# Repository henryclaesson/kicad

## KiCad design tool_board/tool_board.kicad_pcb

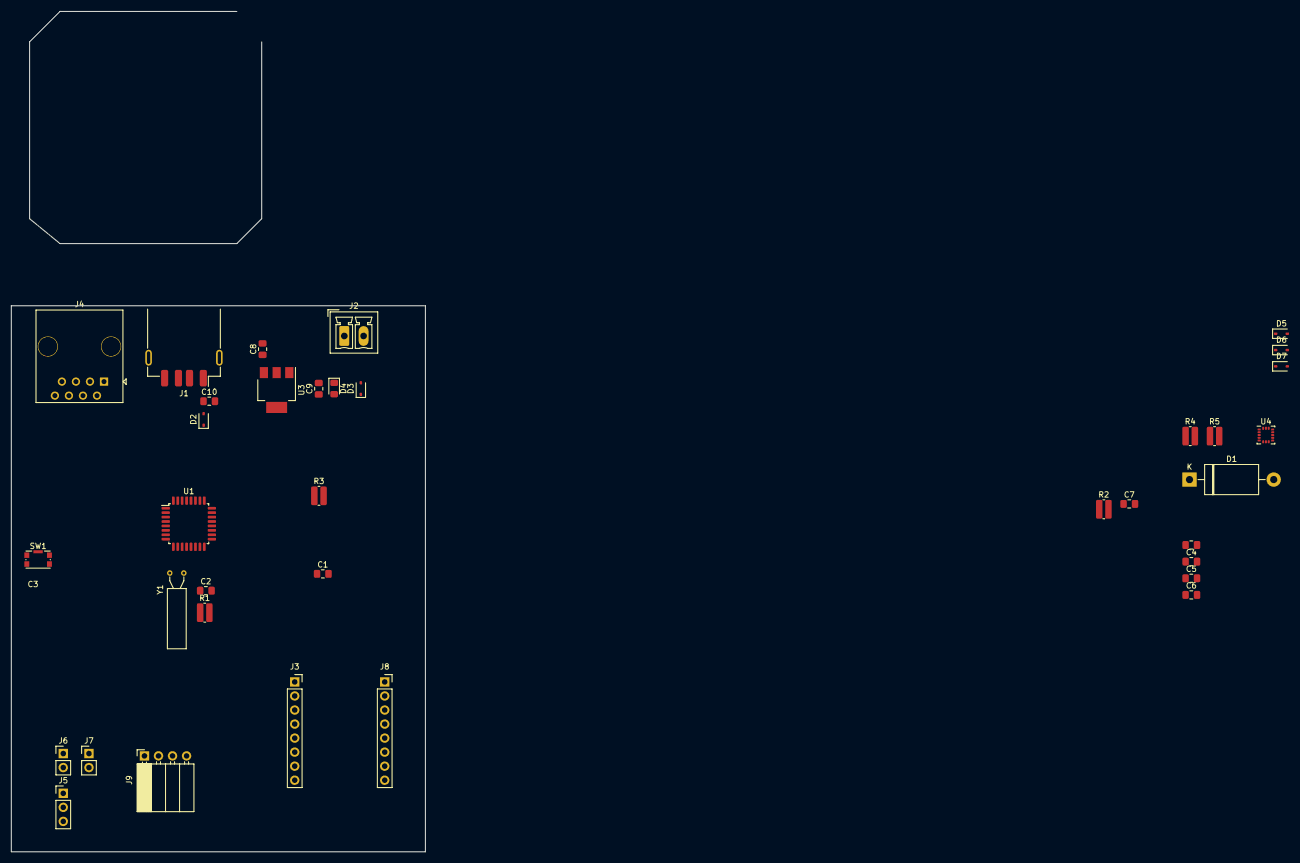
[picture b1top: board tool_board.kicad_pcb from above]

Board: 2 copper layers, 74.9 x 152.1 mm, 36 parts (0 on the bottom side), 32 nets, no tracks yet.

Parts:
C1, C2: 27p; C_0805_2012Metric_Pad1.18x1.45mm_HandSolder
C3, C4, C6, C7: 100nF; C_0805_2012Metric_Pad1.18x1.45mm_HandSolder
C5: 100nF.; C_0805_2012Metric_Pad1.18x1.45mm_HandSolder
C8: 10u; C_0805_2012Metric_Pad1.18x1.45mm_HandSolder
C9: 1uF; C_0805_2012Metric_Pad1.18x1.45mm_HandSolder
C10: 10uF; C_0805_2012Metric_Pad1.18x1.45mm_HandSolder
D1: 1N53xxB; D_DO-201_P15.24mm_Horizontal
D2, D3, D5, D6, D7: 1N5819WS; D_SOD-323
D4: LED; LED_0805_2012Metric_Pad1.15x1.40mm_HandSolder
J1: USB_A; USB_A_Receptacle_GCT_USB1046
J2: 24V Bus; PhoenixContact_MCV_1,5_2-G-3.5_1x02_P3.50mm_Vertical
J3: DRIVER_POWER_RIAL; PinSocket_1x08_P2.54mm_Vertical
J4: Conn_01x08_Socket; RJ45_OST_PJ012-8P8CX_Vertical
J5: Fan; PinHeader_1x03_P2.54mm_Vertical
J6: Temperature Read 1; PinHeader_1x02_P2.54mm_Vertical
J7: Temperature Read 2; PinHeader_1x02_P2.54mm_Vertical
J8: STP_DIR_EN_BUS; PinSocket_1x08_P2.54mm_Vertical
J9: MOTOR_OUTPUT; PinSocket_1x04_P2.54mm_Horizontal
R1: 1K; R_0612_1632Metric_Pad1.18x3.40mm_HandSolder
R2: 100; R_0612_1632Metric_Pad1.18x3.40mm_HandSolder
R3: 1k; R_0612_1632Metric_Pad1.18x3.40mm_HandSolder
R4: 22.1K; R_0612_1632Metric_Pad1.18x3.40mm_HandSolder
R5: 47.5K; R_0612_1632Metric_Pad1.18x3.40mm_HandSolder
SW1: SW_Push_Open_Dual; SW_Push_1P1T-SH_NO_CK_KMR2xxG
U1: ATmega328P-P; LQFP-32_7x7mm_P0.8mm
U3: NCP1117-12_TO252; SOT-223-3_TabPin2
U4: CP2102N-Axx-xQFN20; LGA-16_3x3mm_P0.5mm_LayoutBorder3x5y
Y1: ABLS-12.000MHZ-B4-T; Crystal_AT310_D3.0mm_L10.0mm_Horizontal

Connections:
5V -USB: C3.1, C4.1, C5.1, C6.1, C9.1, C10.1, D2.2 (A), J1.1 (VBUS), J3.7, R3.1, R4.1, U1.7 (VCC), U1.20 (AVCC), U1.21 (AREF), U3.2 (VO), U4.7 (VREGIN)
24v: D3.2 (A), J2.1, J3.1, J5.1
XIN: C1.1, U1.9 (XTAL1/PB6), Y1.2
/USB/3.3V: D5.1 (K), R4.2, R5.1, U4.6 (VDD), U4.8 (VBUS)
A+: J3.6, J9.1
A-: J3.5, J9.2
B+: J3.4, J9.3
B-: J3.3, J9.4
DIR: J8.8, U1.18 (PB4)
EN: J8.1, U1.16 (PB2)
ETH0: J4.1, U1.25 (PC2)
ETH1: J4.2, U1.26 (PC3)
ETH2: J4.3, U1.4 (PD2)
ETH3: J4.4, U1.5 (PD3)
ETH4: J4.5, U1.6 (PD4)
ETH5: J4.6, U1.11 (PD5)
ETH6: J4.7, U1.12 (PD6)
ETH7: J4.8, U1.13 (PD7)
FAN1: J5.2, U1.15 (PB1)
GND: C1.2, C2.2, C3.2, C4.2, C5.2, C6.2, C8.2, C9.2, C10.2, D4.1 (K), D5.2 (A), D6.2 (A), D7.2 (A), J1.4 (GND), J1.5 (Shield), J2.2, J3.2, J3.8, J5.3, J6.2, J7.2, R5.2, SW1.2, U1.8 (GND), U1.22 (GND), U3.1 (GND), U4.3 (GND), U4.12 (GND)
N.C.: C8.1, D2.1 (K), D3.1 (K), U3.3 (VI)
unnamed: C2.1, R1.1, Y1.1
unnamed: D1.1 (K), R2.1
unnamed: D4.2 (A), R3.2
RTS: C7.2, U4.9 (~RST)
Reset: C7.1, D1.2 (A), R2.2, SW1.1, U1.1 (~RESET/PC6)
STEP: J8.7, U1.17 (PB3)
TEMPIN1: J6.1, U1.23 (PC0)
TEMPIN2: J7.1, U1.24 (PC1)
USB+: D7.1 (K), J1.3 (D+), U4.4 (D+)
USB-: D6.1 (K), J1.2 (D-), U4.5 (D-)
XOUT: R1.2, U1.10 (XTAL2/PB7)

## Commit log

2023-12-17 type a message tho
    type a message tho
2023-12-19 message
2024-01-03 back from break
